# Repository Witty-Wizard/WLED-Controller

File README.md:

# Led-Controller  

Review complete , BOM generated , will send for FAB and BOM procurement

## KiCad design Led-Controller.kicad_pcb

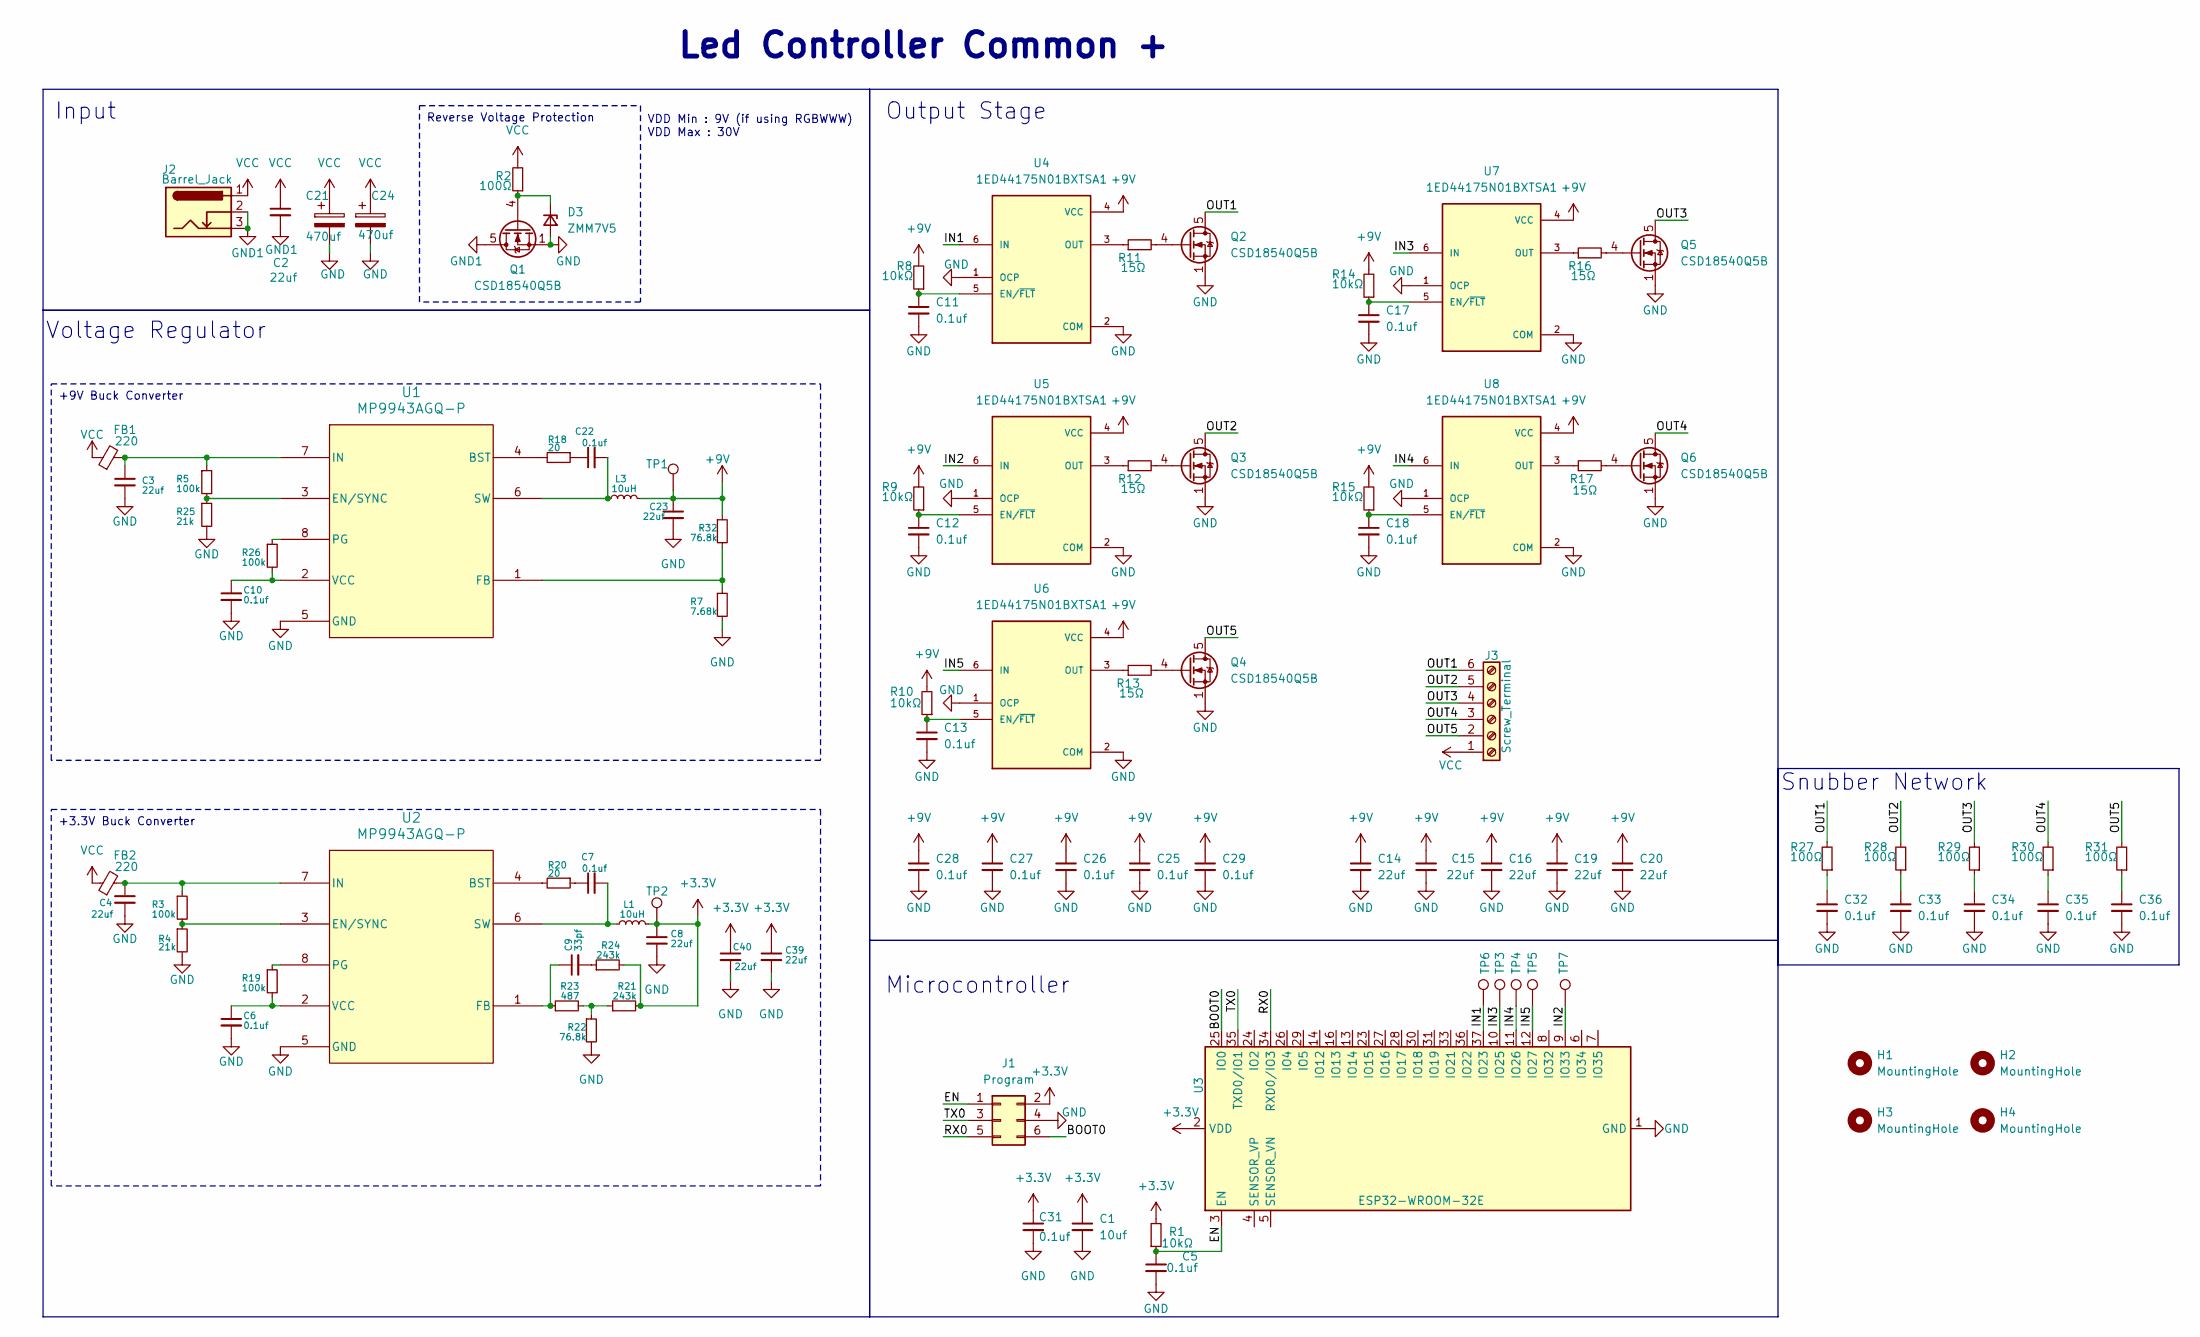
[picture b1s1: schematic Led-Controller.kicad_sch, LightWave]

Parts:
C1: 10uf; C_0603_1608Metric; Part No GRM188R60J106KE47D
C2, C14, C15, C16, C19, C20: 22uf; C_0805_2012Metric; Part No GRM21BR61C226ME44L
C3, C4, C8, C23, C39, C40: 22uf; C_0603_1608Metric; Part No GRM188C61C226ME01W
C5, C6, C7, C10, C11, C12, C13, C17, C18, C22, C31, C32, C33, C34, C35, C36: 0.1uf; C_0603_1608Metric; Part No GCJ188R71C104MA01J
C9: 33pf; C_0603_1608Metric; Part No GCM1885C2A330JA16D
C21, C24: 470uf; CP_Radial_D10.0mm_P2.50mm_P5.00mm; Part No 35PX470MEFC10X12.5
C25, C26, C27, C28, C29: 0.1uf; C_0805_2012Metric; Part No GCM21BR71E104KA37L
D3: ZMM7V5; D_MiniMELF; Part No ZMM7V5
FB1, FB2: 220; L_0603_1608Metric; Part No BLM18RK221SN1D
H1, H2, H3, H4: MountingHole; MountingHole_3.2mm_M3_DIN965_Pad
J1: Program; PinHeader_2x03_P2.54mm_Vertical; Part No 852-40-006-10-003000
J2: Barrel_Jack; BarrelJack_GCT_DCJ200-10-A_Horizontal
J3: Screw_Terminal; TerminalBlock_bornier-6_P5.08mm
L1, L3: 10uH; L_Changjiang_FNR8040S; Part No SRN8040-100M
Q1, Q2, Q3, Q4, Q5, Q6: CSD18540Q5B; TDSON-8-1; Part No CSD18540Q5B
R1, R8, R9, R10, R14, R15: 10kΩ; R_0603_1608Metric; Part No RC0603FR-0710KL
R2, R27, R28, R29, R30, R31: 100Ω; R_0603_1608Metric; Part No RC0603FR-07100RL
R3, R5, R19, R26: 100k; R_0603_1608Metric; Part No RC0603FR-07100KL
R4, R25: 21k; R_0603_1608Metric; Part No RC0603FR-0721KL
R7: 7.68k; R_0603_1608Metric; Part No RC0603FR-077K68L
R11, R12, R13, R16, R17: 15Ω; R_0603_1608Metric; Part No RC0603FR-0715RL
R18, R20: 20; R_0603_1608Metric; Part No RC0603JR-0720RL
R21, R24: 243k; R_0603_1608Metric; Part No RC0603FR-07243KL
R22, R32: 76.8k; R_0603_1608Metric; Part No RC0603FR-0776K8L
R23: 487; R_0603_1608Metric; Part No RC0603FR-07487RL
TP1, TP2, TP3, TP4, TP5, TP6, TP7: TestPoint_Pad_D1.0mm
U1, U2: MP9943AGQ-P; MP9943A; Part No MP9943AGQ-P
U3: ESP32-WROOM-32E; ESP32-WROOM-32D; Part No ESP32-WROOM-32E-N8
U4, U5, U6, U7, U8: 1ED44175N01BXTSA1; Part No 1ED44175N01BXTSA1

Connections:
+3.3V: C1.1, C8.1, C31.1, C39.1, C40.1, J1.2, L1.2, R1.2, R21.2, R24.2, TP2.1 (1_1), U3.2 (VDD)
+9V: C14.1, C15.1, C16.1, C19.1, C20.1, C23.1, C25.1, C26.1, C27.1, C28.1, C29.1, L3.2, R8.2, R9.2, R10.2, R14.2, R15.2, R32.1, TP1.1 (1_1), U4.4 (VCC), U5.4 (VCC), U6.4 (VCC), U7.4 (VCC), U8.4 (VCC)
/BOOT0: J1.6, U3.25 (IO0)
/EN: C5.1, J1.1, R1.1, U3.3 (EN)
/IN1: TP6.1 (1_1), U3.37 (IO23), U4.6 (IN)
/IN2: TP7.1 (1_1), U3.9 (IO33), U5.6 (IN)
/IN3: TP3.1 (1_1), U3.10 (IO25), U7.6 (IN)
/IN4: TP4.1 (1_1), U3.11 (IO26), U8.6 (IN)
/IN5: TP5.1 (1_1), U3.12 (IO27), U6.6 (IN)
/OUT1: J3.6, Q2.5 (D), R27.2
/OUT2: J3.5, Q3.5 (D), R28.2
/OUT3: J3.4, Q5.5 (D), R29.2
/OUT4: J3.3, Q6.5 (D), R30.2
/OUT5: J3.2, Q4.5 (D), R31.2
/RX0: J1.5, U3.34 (RXD0/IO3)
/TX0: J1.3, U3.35 (TXD0/IO1)
GND: C1.2, C3.2, C4.2, C5.2, C6.2, C8.2, C10.2, C11.2, C12.2, C13.2, C14.2, C15.2, C16.2, C17.2, C18.2, C19.2, C20.2, C21.2, C23.2, C24.2, C25.2, C26.2, C27.2, C28.2, C29.2, C31.2, C32.2, C33.2, C34.2, C35.2, C36.2, C39.2, C40.2, D3.2 (A), J1.4, Q1.1 (S), Q1.2 (S), Q1.3 (S), Q2.1 (S), Q2.2 (S), Q2.3 (S), Q3.1 (S), Q3.2 (S), Q3.3 (S), Q4.1 (S), Q4.2 (S), Q4.3 (S), Q5.1 (S), Q5.2 (S), Q5.3 (S), Q6.1 (S), Q6.2 (S), Q6.3 (S), R4.2, R7.2, R22.2, R25.2, U1.5 (GND), U2.5 (GND), U3.1 (GND), U3.15 (GND), U3.38 (GND), U3.39 (GND), U4.1 (OCP), U4.2 (COM), U5.1 (OCP), U5.2 (COM), U6.1 (OCP), U6.2 (COM), U7.1 (OCP), U7.2 (COM), U8.1 (OCP), U8.2 (COM)
GND1: C2.2, J2.2, J2.3, Q1.5 (D)
unnamed: C7.1, R20.1
unnamed: C9.2, R24.1
unnamed: C22.1, R18.1
unnamed: C32.1, R27.1
unnamed: C33.1, R28.1
unnamed: C34.1, R29.1
unnamed: C35.1, R30.1
unnamed: C36.1, R31.1
unnamed: D3.1 (K), Q1.4 (G), R2.1
unnamed: Q2.4 (G), R11.2
unnamed: Q3.4 (G), R12.2
unnamed: Q4.4 (G), R13.2
unnamed: Q5.4 (G), R16.2
unnamed: Q6.4 (G), R17.2
unnamed: R21.1, R22.1, R23.2
unnamed: R18.2, U1.4 (BST)
unnamed: R5.2, R25.1, U1.3 (EN/SYNC)
unnamed: R7.1, R32.2, U1.1 (FB)
unnamed: C3.1, FB1.2, R5.1, U1.7 (IN)
unnamed: R26.1, U1.8 (PG)
unnamed: C22.2, L3.1, U1.6 (SW)
unnamed: C10.1, R26.2, U1.2 (VCC)
unnamed: R20.2, U2.4 (BST)
unnamed: R3.2, R4.1, U2.3 (EN/SYNC)
unnamed: C9.1, R23.1, U2.1 (FB)
unnamed: C4.1, FB2.2, R3.1, U2.7 (IN)
unnamed: R19.1, U2.8 (PG)
unnamed: C7.2, L1.1, U2.6 (SW)
unnamed: C6.1, R19.2, U2.2 (VCC)
unnamed: C11.1, R8.1, U4.5 (EN/~FLT)
unnamed: R11.1, U4.3 (OUT)
unnamed: C12.1, R9.1, U5.5 (EN/~FLT)
unnamed: R12.1, U5.3 (OUT)
unnamed: C13.1, R10.1, U6.5 (EN/~FLT)
unnamed: R13.1, U6.3 (OUT)
unnamed: C17.1, R14.1, U7.5 (EN/~FLT)
unnamed: R16.1, U7.3 (OUT)
unnamed: C18.1, R15.1, U8.5 (EN/~FLT)
unnamed: R17.1, U8.3 (OUT)
VCC: C2.1, C21.1, C24.1, FB1.1, FB2.1, J2.1, J3.1, R2.2

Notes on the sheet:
Input
Snubber Network
Voltage Regulator
VDD Min : 9V (if using RGBWWW) VDD Max : 30V
Output Stage
Microcontroller
Led Controller Common +
Reverse Voltage Protection
+9V Buck Converter
+3.3V Buck Converter

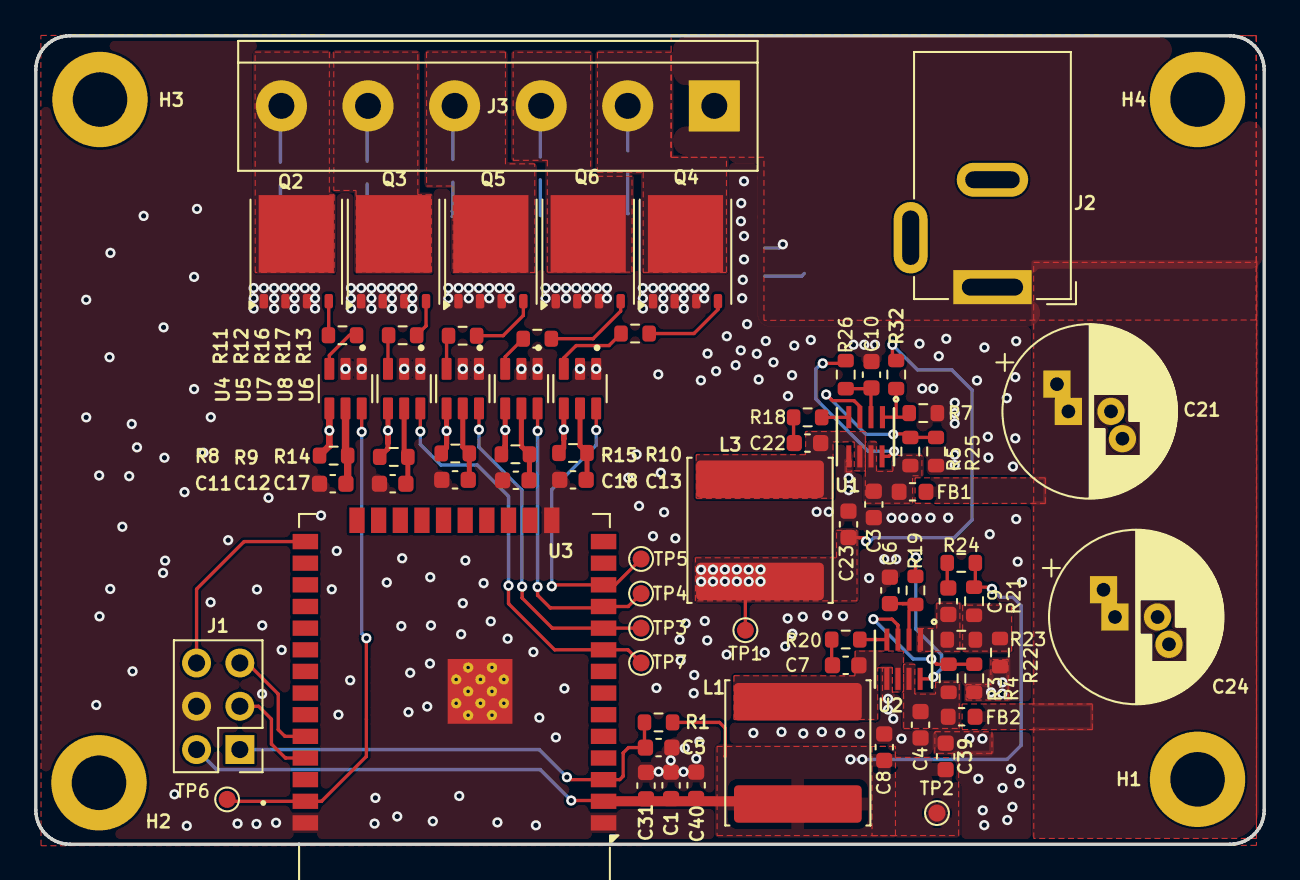
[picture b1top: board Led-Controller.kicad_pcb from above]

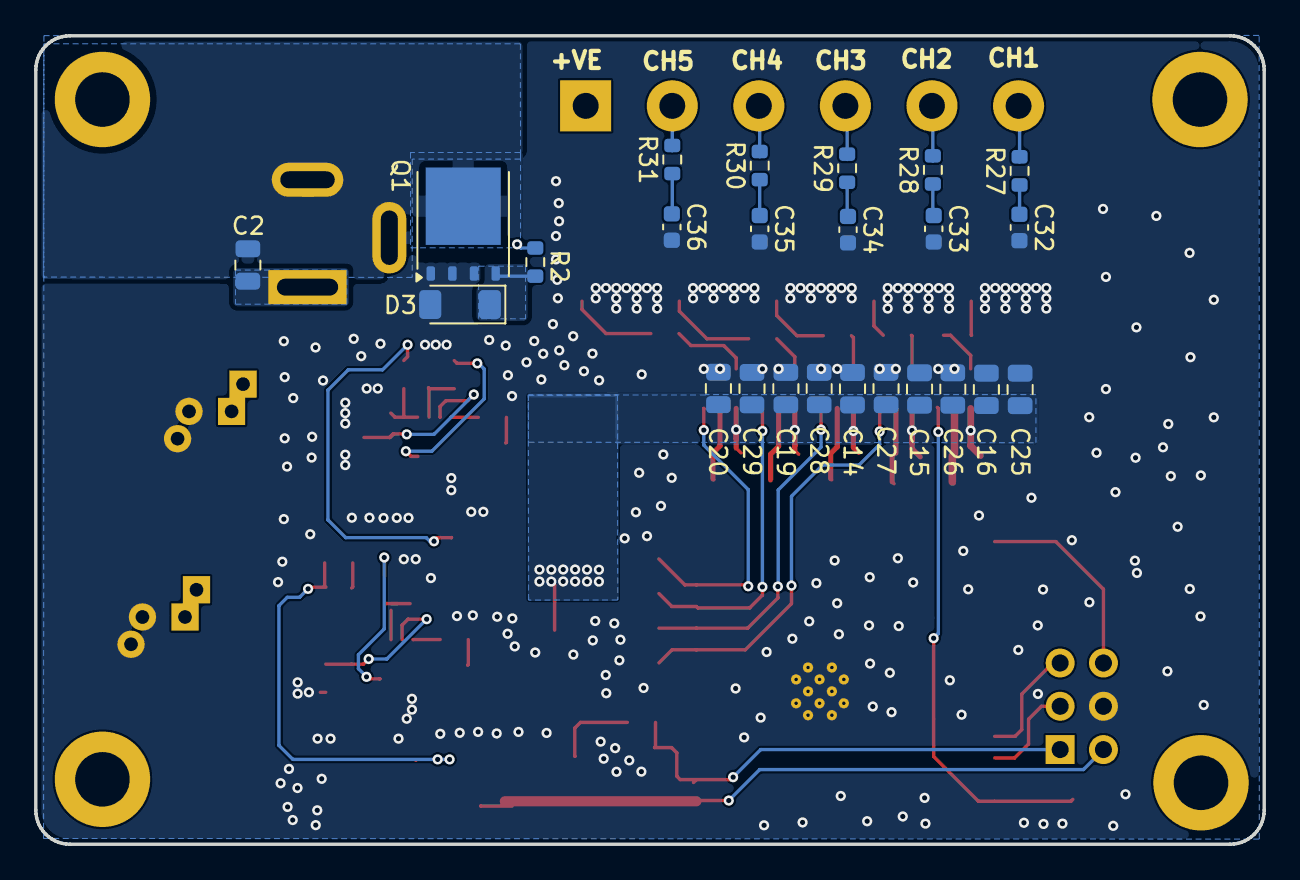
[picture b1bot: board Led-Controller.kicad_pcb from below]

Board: 2 copper layers, 72.1 x 47.4 mm, 101 parts (24 on the bottom side), 58 nets.

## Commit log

2025-03-20 Added: Grounded Mounting Holes (That aren't actually grounded, LOL)
2025-03-22 Added: Enclosure STEP FIle
2025-04-08 Exported BOM
2025-06-06 Added: New power stage
2025-06-12 Added: new Inductor
2025-06-13 Minor fixes and layout changes
2025-06-20 Fixed DFM Issues
2026-01-16 review pending
2026-01-16 Review done
2026-01-19 WIP::Added: BOM for major components
2026-01-24 review still pending , BOM finalized and changed to 0603
2026-01-24 corrected JOB SET to generate correct BOM
2026-01-24 Fixed::BOM: Fixed unconsistencies in BOM
2026-01-26 silk screen changes + review done
2026-01-29 updated files according to FAb feedback and capabilities
2026-02-01 drill files were missing from jobset
2026-02-14 Fix::Voltage Reg and LED Pin
2026-02-15 Added: Bare ESP32 Chip
2026-04-08 Removed WS2812 Connector
2026-04-15 Did Producion changes
2026-04-29 Fixed: 3D Models
